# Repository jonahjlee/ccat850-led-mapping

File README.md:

# ccat850-led-mapping
CAD files for CCAT 850GHz LED mapping array PCB &amp; peripherals

This project contains various cad files relating to hardware required to perform LED mapping for CCAT's 850GHz module.
This project includes the following directories:
- ``led_mapper_850``
  - The defining the PCB for one rhombus of the LED mapper array. Contains the KiCAD project and some Python programs used to automate the LED/via/track layout.
- ``multiplexer`` - NO LONGER USED
  - The cable splitter used between the Arduino shield and the mapper array. Splits the inputs into 13 parallel 24-pin connectors. Since the PCB has been updated to use a single connector, this is no longer relevant to the project.
- ``collimator``
  - SOLIDWORKS CAD files for the collimator, which mounts to the array and nests each LED such that light is funneled one-to-one with the feedhorns. The old collimator CAD model can be found in [this onshape project](https://cad.onshape.com/documents/4a9874995d3b4039a34f4491/w/a61d1c1f9ee3ea8193c6d7eb/e/afbea4677e4648f6492246a2).

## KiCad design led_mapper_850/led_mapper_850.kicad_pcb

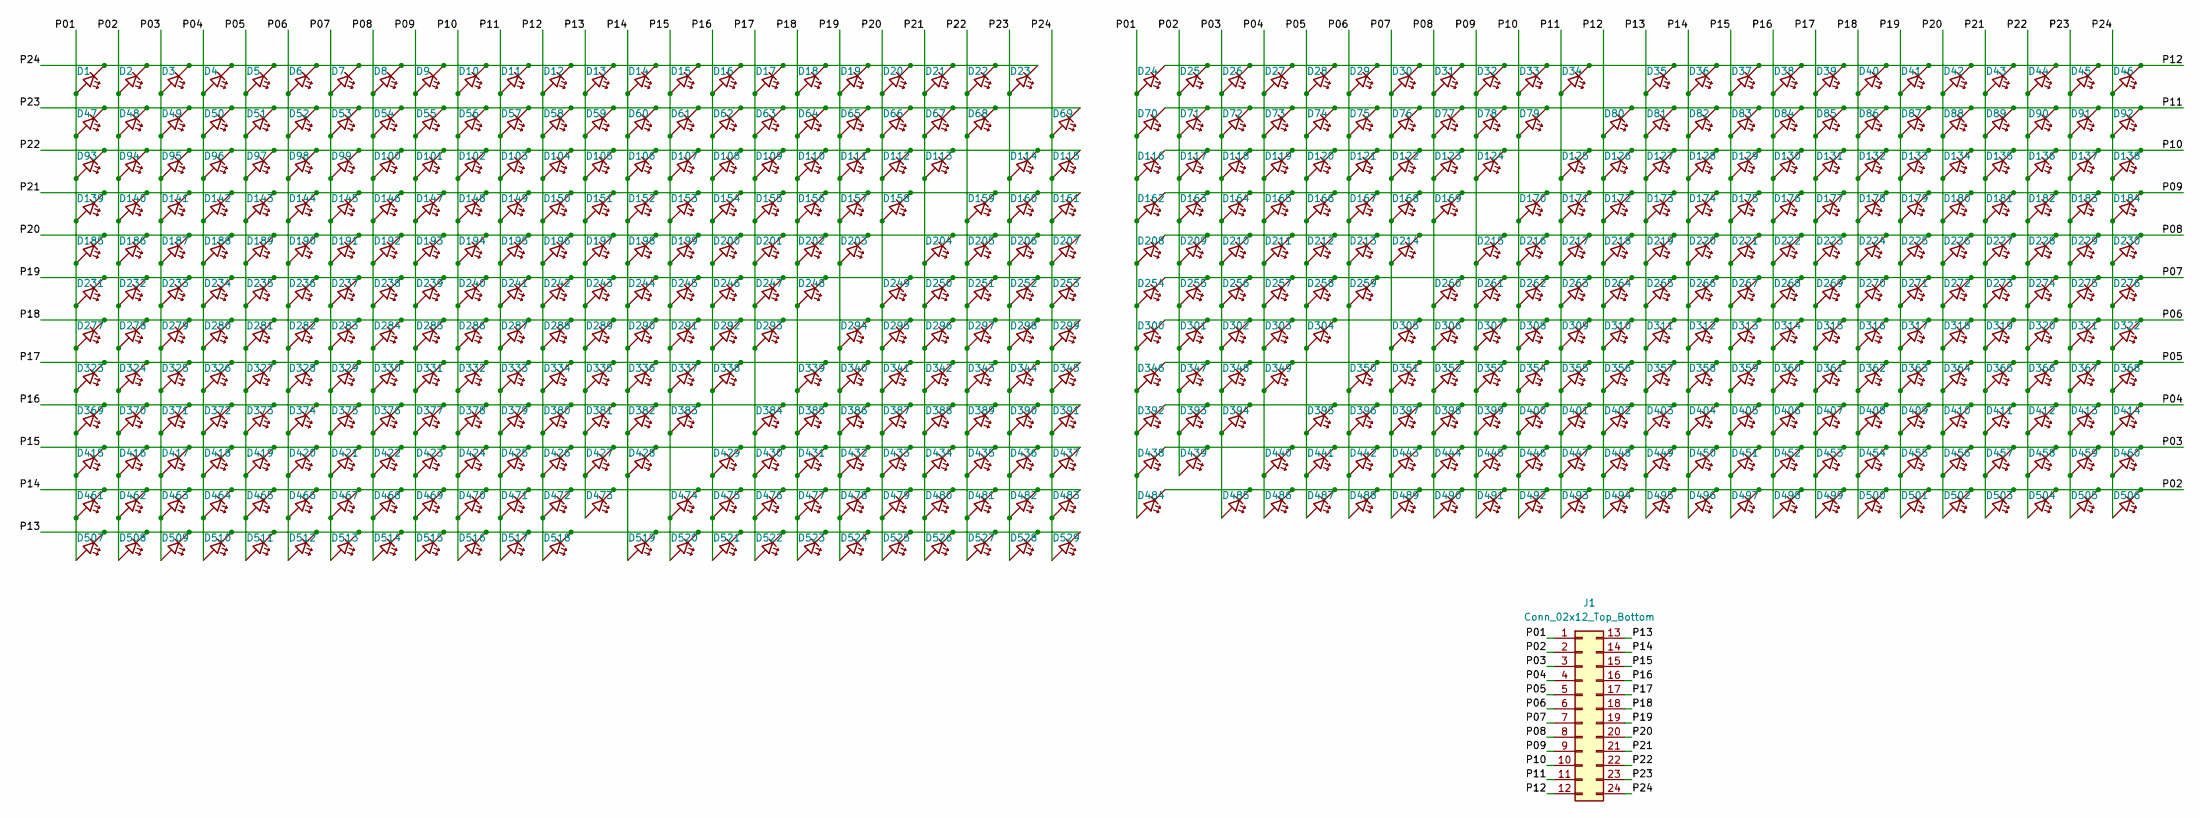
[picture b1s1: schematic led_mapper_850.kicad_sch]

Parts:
D1, D2, D3, D4, D5, D6, D7, D8, D9, D10, D11, D12, D13, D14, D15, D16, D17, D18, D19, D20, D21, D22, D23, D24, D25, D26, D27, D28, D29, D30, D31, D32, D33, D34, D35, D36, D37, D38, D39, D40, D41, D42, D43, D44, D45, D46, D47, D48, D49, D50, D51, D52, D53, D54, D55, D56, D57, D58, D59, D60, D61, D62, D63, D64, D65, D66, D67, D68, D69, D70, D71, D72, D73, D74, D75, D76, D77, D78, D79, D80, D81, D82, D83, D84, D85, D86, D87, D88, D89, D90, D91, D92, D93, D94, D95, D96, D97, D98, D99, D100, D101, D102, D103, D104, D105, D106, D107, D108, D109, D110, D111, D112, D113, D114, D115, D116, D117, D118, D119, D120, D121, D122, D123, D124, D125, D126, D127, D128, D129, D130, D131, D132, D133, D134, D135, D136, D137, D138, D139, D140, D141, D142, D143, D144, D145, D146, D147, D148, D149, D150, D151, D152, D153, D154, D155, D156, D157, D158, D159, D160, D161, D162, D163, D164, D165, D166, D167, D168, D169, D170, D171, D172, D173, D174, D175, D176, D177, D178, D179, D180, D181, D182, D183, D184, D185, D186, D187, D188, D189, D190, D191, D192, D193, D194, D195, D196, D197, D198, D199, D200, D201, D202, D203, D204, D205, D206, D207, D208, D209, D210, D211, D212, D213, D214, D215, D216, D217, D218, D219, D220, D221, D222, D223, D224, D225, D226, D227, D228, D229, D230, D231, D232, D233, D234, D235, D236, D237, D238, D239, D240, D241, D242, D243, D244, D245, D246, D247, D248, D249, D250, D251, D252, D253, D254, D255, D256, D257, D258, D259, D260, D261, D262, D263, D264, D265, D266, D267, D268, D269, D270, D271, D272, D273, D274, D275, D276, D277, D278, D279, D280, D281, D282, D283, D284, D285, D286, D287, D288, D289, D290, D291, D292, D293, D294, D295, D296, D297, D298, D299, D300, D301, D302, D303, D304, D305, D306, D307, D308, D309, D310, D311, D312, D313, D314, D315, D316, D317, D318, D319, D320, D321, D322, D323, D324, D325, D326, D327, D328, D329, D330, D331, D332, D333, D334, D335, D336, D337, D338, D339, D340, D341, D342, D343, D344, D345, D346, D347, D348, D349, D350, D351, D352, D353, D354, D355, D356, D357, D358, D359, D360, D361, D362, D363, D364, D365, D366, D367, D368, D369, D370, D371, D372, D373, D374, D375, D376, D377, D378, D379, D380, D381, D382, D383, D384, D385, D386, D387, D388, D389, D390, D391, D392, D393, D394, D395, D396, D397, D398, D399, D400, D401, D402, D403, D404, D405, D406, D407, D408, D409, D410, D411, D412, D413, D414, D415, D416, D417, D418, D419, D420, D421, D422, D423, D424, D425, D426, D427, D428, D429, D430, D431, D432, D433, D434, D435, D436, D437, D438, D439, D440, D441, D442, D443, D444, D445, D446, D447, D448, D449, D450, D451, D452, D453, D454, D455, D456, D457, D458, D459, D460, D461, D462, D463, D464, D465, D466, D467, D468, D469, D470, D471, D472, D473, D474, D475, D476, D477, D478, D479, D480, D481, D482, D483, D484, D485, D486, D487, D488, D489, D490, D491, D492, D493, D494, D495, D496, D497, D498, D499, D500, D501, D502, D503, D504, D505, D506, D507, D508, D509, D510, D511, D512, D513, D514, D515, D516, D517, D518, D519, D520, D521, D522, D523, D524, D525, D526, D527, D528, D529: LED; LED_0201_0603Metric
J1: Conn_02x12_Top_Bottom; PinSocket_2x12_P2.54mm_Vertical_SMD_custom

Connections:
/P01: D1.2 (A), D24.2 (A), D47.2 (A), D70.2 (A), D93.2 (A), D116.2 (A), D139.2 (A), D162.2 (A), D185.2 (A), D208.2 (A), D231.2 (A), D254.2 (A), D277.2 (A), D300.2 (A), D323.2 (A), D346.2 (A), D369.2 (A), D392.2 (A), D415.2 (A), D438.2 (A), D461.2 (A), D484.2 (A), D507.2 (A), J1.1
/P02: D2.2 (A), D25.2 (A), D48.2 (A), D71.2 (A), D94.2 (A), D117.2 (A), D140.2 (A), D163.2 (A), D186.2 (A), D209.2 (A), D232.2 (A), D255.2 (A), D278.2 (A), D301.2 (A), D324.2 (A), D347.2 (A), D370.2 (A), D393.2 (A), D416.2 (A), D439.2 (A), D462.2 (A), D484.1 (K), D485.1 (K), D486.1 (K), D487.1 (K), D488.1 (K), D489.1 (K), D490.1 (K), D491.1 (K), D492.1 (K), D493.1 (K), D494.1 (K), D495.1 (K), D496.1 (K), D497.1 (K), D498.1 (K), D499.1 (K), D500.1 (K), D501.1 (K), D502.1 (K), D503.1 (K), D504.1 (K), D505.1 (K), D506.1 (K), D508.2 (A), J1.2
/P03: D3.2 (A), D26.2 (A), D49.2 (A), D72.2 (A), D95.2 (A), D118.2 (A), D141.2 (A), D164.2 (A), D187.2 (A), D210.2 (A), D233.2 (A), D256.2 (A), D279.2 (A), D302.2 (A), D325.2 (A), D348.2 (A), D371.2 (A), D394.2 (A), D417.2 (A), D438.1 (K), D439.1 (K), D440.1 (K), D441.1 (K), D442.1 (K), D443.1 (K), D444.1 (K), D445.1 (K), D446.1 (K), D447.1 (K), D448.1 (K), D449.1 (K), D450.1 (K), D451.1 (K), D452.1 (K), D453.1 (K), D454.1 (K), D455.1 (K), D456.1 (K), D457.1 (K), D458.1 (K), D459.1 (K), D460.1 (K), D463.2 (A), D485.2 (A), D509.2 (A), J1.3
/P04: D4.2 (A), D27.2 (A), D50.2 (A), D73.2 (A), D96.2 (A), D119.2 (A), D142.2 (A), D165.2 (A), D188.2 (A), D211.2 (A), D234.2 (A), D257.2 (A), D280.2 (A), D303.2 (A), D326.2 (A), D349.2 (A), D372.2 (A), D392.1 (K), D393.1 (K), D394.1 (K), D395.1 (K), D396.1 (K), D397.1 (K), D398.1 (K), D399.1 (K), D400.1 (K), D401.1 (K), D402.1 (K), D403.1 (K), D404.1 (K), D405.1 (K), D406.1 (K), D407.1 (K), D408.1 (K), D409.1 (K), D410.1 (K), D411.1 (K), D412.1 (K), D413.1 (K), D414.1 (K), D418.2 (A), D440.2 (A), D464.2 (A), D486.2 (A), D510.2 (A), J1.4
/P05: D5.2 (A), D28.2 (A), D51.2 (A), D74.2 (A), D97.2 (A), D120.2 (A), D143.2 (A), D166.2 (A), D189.2 (A), D212.2 (A), D235.2 (A), D258.2 (A), D281.2 (A), D304.2 (A), D327.2 (A), D346.1 (K), D347.1 (K), D348.1 (K), D349.1 (K), D350.1 (K), D351.1 (K), D352.1 (K), D353.1 (K), D354.1 (K), D355.1 (K), D356.1 (K), D357.1 (K), D358.1 (K), D359.1 (K), D360.1 (K), D361.1 (K), D362.1 (K), D363.1 (K), D364.1 (K), D365.1 (K), D366.1 (K), D367.1 (K), D368.1 (K), D373.2 (A), D395.2 (A), D419.2 (A), D441.2 (A), D465.2 (A), D487.2 (A), D511.2 (A), J1.5
/P06: D6.2 (A), D29.2 (A), D52.2 (A), D75.2 (A), D98.2 (A), D121.2 (A), D144.2 (A), D167.2 (A), D190.2 (A), D213.2 (A), D236.2 (A), D259.2 (A), D282.2 (A), D300.1 (K), D301.1 (K), D302.1 (K), D303.1 (K), D304.1 (K), D305.1 (K), D306.1 (K), D307.1 (K), D308.1 (K), D309.1 (K), D310.1 (K), D311.1 (K), D312.1 (K), D313.1 (K), D314.1 (K), D315.1 (K), D316.1 (K), D317.1 (K), D318.1 (K), D319.1 (K), D320.1 (K), D321.1 (K), D322.1 (K), D328.2 (A), D350.2 (A), D374.2 (A), D396.2 (A), D420.2 (A), D442.2 (A), D466.2 (A), D488.2 (A), D512.2 (A), J1.6
/P07: D7.2 (A), D30.2 (A), D53.2 (A), D76.2 (A), D99.2 (A), D122.2 (A), D145.2 (A), D168.2 (A), D191.2 (A), D214.2 (A), D237.2 (A), D254.1 (K), D255.1 (K), D256.1 (K), D257.1 (K), D258.1 (K), D259.1 (K), D260.1 (K), D261.1 (K), D262.1 (K), D263.1 (K), D264.1 (K), D265.1 (K), D266.1 (K), D267.1 (K), D268.1 (K), D269.1 (K), D270.1 (K), D271.1 (K), D272.1 (K), D273.1 (K), D274.1 (K), D275.1 (K), D276.1 (K), D283.2 (A), D305.2 (A), D329.2 (A), D351.2 (A), D375.2 (A), D397.2 (A), D421.2 (A), D443.2 (A), D467.2 (A), D489.2 (A), D513.2 (A), J1.7
/P08: D8.2 (A), D31.2 (A), D54.2 (A), D77.2 (A), D100.2 (A), D123.2 (A), D146.2 (A), D169.2 (A), D192.2 (A), D208.1 (K), D209.1 (K), D210.1 (K), D211.1 (K), D212.1 (K), D213.1 (K), D214.1 (K), D215.1 (K), D216.1 (K), D217.1 (K), D218.1 (K), D219.1 (K), D220.1 (K), D221.1 (K), D222.1 (K), D223.1 (K), D224.1 (K), D225.1 (K), D226.1 (K), D227.1 (K), D228.1 (K), D229.1 (K), D230.1 (K), D238.2 (A), D260.2 (A), D284.2 (A), D306.2 (A), D330.2 (A), D352.2 (A), D376.2 (A), D398.2 (A), D422.2 (A), D444.2 (A), D468.2 (A), D490.2 (A), D514.2 (A), J1.8
/P09: D9.2 (A), D32.2 (A), D55.2 (A), D78.2 (A), D101.2 (A), D124.2 (A), D147.2 (A), D162.1 (K), D163.1 (K), D164.1 (K), D165.1 (K), D166.1 (K), D167.1 (K), D168.1 (K), D169.1 (K), D170.1 (K), D171.1 (K), D172.1 (K), D173.1 (K), D174.1 (K), D175.1 (K), D176.1 (K), D177.1 (K), D178.1 (K), D179.1 (K), D180.1 (K), D181.1 (K), D182.1 (K), D183.1 (K), D184.1 (K), D193.2 (A), D215.2 (A), D239.2 (A), D261.2 (A), D285.2 (A), D307.2 (A), D331.2 (A), D353.2 (A), D377.2 (A), D399.2 (A), D423.2 (A), D445.2 (A), D469.2 (A), D491.2 (A), D515.2 (A), J1.9
/P10: D10.2 (A), D33.2 (A), D56.2 (A), D79.2 (A), D102.2 (A), D116.1 (K), D117.1 (K), D118.1 (K), D119.1 (K), D120.1 (K), D121.1 (K), D122.1 (K), D123.1 (K), D124.1 (K), D125.1 (K), D126.1 (K), D127.1 (K), D128.1 (K), D129.1 (K), D130.1 (K), D131.1 (K), D132.1 (K), D133.1 (K), D134.1 (K), D135.1 (K), D136.1 (K), D137.1 (K), D138.1 (K), D148.2 (A), D170.2 (A), D194.2 (A), D216.2 (A), D240.2 (A), D262.2 (A), D286.2 (A), D308.2 (A), D332.2 (A), D354.2 (A), D378.2 (A), D400.2 (A), D424.2 (A), D446.2 (A), D470.2 (A), D492.2 (A), D516.2 (A), J1.10
/P11: D11.2 (A), D34.2 (A), D57.2 (A), D70.1 (K), D71.1 (K), D72.1 (K), D73.1 (K), D74.1 (K), D75.1 (K), D76.1 (K), D77.1 (K), D78.1 (K), D79.1 (K), D80.1 (K), D81.1 (K), D82.1 (K), D83.1 (K), D84.1 (K), D85.1 (K), D86.1 (K), D87.1 (K), D88.1 (K), D89.1 (K), D90.1 (K), D91.1 (K), D92.1 (K), D103.2 (A), D125.2 (A), D149.2 (A), D171.2 (A), D195.2 (A), D217.2 (A), D241.2 (A), D263.2 (A), D287.2 (A), D309.2 (A), D333.2 (A), D355.2 (A), D379.2 (A), D401.2 (A), D425.2 (A), D447.2 (A), D471.2 (A), D493.2 (A), D517.2 (A), J1.11
/P12: D12.2 (A), D24.1 (K), D25.1 (K), D26.1 (K), D27.1 (K), D28.1 (K), D29.1 (K), D30.1 (K), D31.1 (K), D32.1 (K), D33.1 (K), D34.1 (K), D35.1 (K), D36.1 (K), D37.1 (K), D38.1 (K), D39.1 (K), D40.1 (K), D41.1 (K), D42.1 (K), D43.1 (K), D44.1 (K), D45.1 (K), D46.1 (K), D58.2 (A), D80.2 (A), D104.2 (A), D126.2 (A), D150.2 (A), D172.2 (A), D196.2 (A), D218.2 (A), D242.2 (A), D264.2 (A), D288.2 (A), D310.2 (A), D334.2 (A), D356.2 (A), D380.2 (A), D402.2 (A), D426.2 (A), D448.2 (A), D472.2 (A), D494.2 (A), D518.2 (A), J1.12
/P13: D13.2 (A), D35.2 (A), D59.2 (A), D81.2 (A), D105.2 (A), D127.2 (A), D151.2 (A), D173.2 (A), D197.2 (A), D219.2 (A), D243.2 (A), D265.2 (A), D289.2 (A), D311.2 (A), D335.2 (A), D357.2 (A), D381.2 (A), D403.2 (A), D427.2 (A), D449.2 (A), D473.2 (A), D495.2 (A), D507.1 (K), D508.1 (K), D509.1 (K), D510.1 (K), D511.1 (K), D512.1 (K), D513.1 (K), D514.1 (K), D515.1 (K), D516.1 (K), D517.1 (K), D518.1 (K), D519.1 (K), D520.1 (K), D521.1 (K), D522.1 (K), D523.1 (K), D524.1 (K), D525.1 (K), D526.1 (K), D527.1 (K), D528.1 (K), D529.1 (K), J1.13
/P14: D14.2 (A), D36.2 (A), D60.2 (A), D82.2 (A), D106.2 (A), D128.2 (A), D152.2 (A), D174.2 (A), D198.2 (A), D220.2 (A), D244.2 (A), D266.2 (A), D290.2 (A), D312.2 (A), D336.2 (A), D358.2 (A), D382.2 (A), D404.2 (A), D428.2 (A), D450.2 (A), D461.1 (K), D462.1 (K), D463.1 (K), D464.1 (K), D465.1 (K), D466.1 (K), D467.1 (K), D468.1 (K), D469.1 (K), D470.1 (K), D471.1 (K), D472.1 (K), D473.1 (K), D474.1 (K), D475.1 (K), D476.1 (K), D477.1 (K), D478.1 (K), D479.1 (K), D480.1 (K), D481.1 (K), D482.1 (K), D483.1 (K), D496.2 (A), D519.2 (A), J1.14
/P15: D15.2 (A), D37.2 (A), D61.2 (A), D83.2 (A), D107.2 (A), D129.2 (A), D153.2 (A), D175.2 (A), D199.2 (A), D221.2 (A), D245.2 (A), D267.2 (A), D291.2 (A), D313.2 (A), D337.2 (A), D359.2 (A), D383.2 (A), D405.2 (A), D415.1 (K), D416.1 (K), D417.1 (K), D418.1 (K), D419.1 (K), D420.1 (K), D421.1 (K), D422.1 (K), D423.1 (K), D424.1 (K), D425.1 (K), D426.1 (K), D427.1 (K), D428.1 (K), D429.1 (K), D430.1 (K), D431.1 (K), D432.1 (K), D433.1 (K), D434.1 (K), D435.1 (K), D436.1 (K), D437.1 (K), D451.2 (A), D474.2 (A), D497.2 (A), D520.2 (A), J1.15
/P16: D16.2 (A), D38.2 (A), D62.2 (A), D84.2 (A), D108.2 (A), D130.2 (A), D154.2 (A), D176.2 (A), D200.2 (A), D222.2 (A), D246.2 (A), D268.2 (A), D292.2 (A), D314.2 (A), D338.2 (A), D360.2 (A), D369.1 (K), D370.1 (K), D371.1 (K), D372.1 (K), D373.1 (K), D374.1 (K), D375.1 (K), D376.1 (K), D377.1 (K), D378.1 (K), D379.1 (K), D380.1 (K), D381.1 (K), D382.1 (K), D383.1 (K), D384.1 (K), D385.1 (K), D386.1 (K), D387.1 (K), D388.1 (K), D389.1 (K), D390.1 (K), D391.1 (K), D406.2 (A), D429.2 (A), D452.2 (A), D475.2 (A), D498.2 (A), D521.2 (A), J1.16
/P17: D17.2 (A), D39.2 (A), D63.2 (A), D85.2 (A), D109.2 (A), D131.2 (A), D155.2 (A), D177.2 (A), D201.2 (A), D223.2 (A), D247.2 (A), D269.2 (A), D293.2 (A), D315.2 (A), D323.1 (K), D324.1 (K), D325.1 (K), D326.1 (K), D327.1 (K), D328.1 (K), D329.1 (K), D330.1 (K), D331.1 (K), D332.1 (K), D333.1 (K), D334.1 (K), D335.1 (K), D336.1 (K), D337.1 (K), D338.1 (K), D339.1 (K), D340.1 (K), D341.1 (K), D342.1 (K), D343.1 (K), D344.1 (K), D345.1 (K), D361.2 (A), D384.2 (A), D407.2 (A), D430.2 (A), D453.2 (A), D476.2 (A), D499.2 (A), D522.2 (A), J1.17
/P18: D18.2 (A), D40.2 (A), D64.2 (A), D86.2 (A), D110.2 (A), D132.2 (A), D156.2 (A), D178.2 (A), D202.2 (A), D224.2 (A), D248.2 (A), D270.2 (A), D277.1 (K), D278.1 (K), D279.1 (K), D280.1 (K), D281.1 (K), D282.1 (K), D283.1 (K), D284.1 (K), D285.1 (K), D286.1 (K), D287.1 (K), D288.1 (K), D289.1 (K), D290.1 (K), D291.1 (K), D292.1 (K), D293.1 (K), D294.1 (K), D295.1 (K), D296.1 (K), D297.1 (K), D298.1 (K), D299.1 (K), D316.2 (A), D339.2 (A), D362.2 (A), D385.2 (A), D408.2 (A), D431.2 (A), D454.2 (A), D477.2 (A), D500.2 (A), D523.2 (A), J1.18
/P19: D19.2 (A), D41.2 (A), D65.2 (A), D87.2 (A), D111.2 (A), D133.2 (A), D157.2 (A), D179.2 (A), D203.2 (A), D225.2 (A), D231.1 (K), D232.1 (K), D233.1 (K), D234.1 (K), D235.1 (K), D236.1 (K), D237.1 (K), D238.1 (K), D239.1 (K), D240.1 (K), D241.1 (K), D242.1 (K), D243.1 (K), D244.1 (K), D245.1 (K), D246.1 (K), D247.1 (K), D248.1 (K), D249.1 (K), D250.1 (K), D251.1 (K), D252.1 (K), D253.1 (K), D271.2 (A), D294.2 (A), D317.2 (A), D340.2 (A), D363.2 (A), D386.2 (A), D409.2 (A), D432.2 (A), D455.2 (A), D478.2 (A), D501.2 (A), D524.2 (A), J1.19
/P20: D20.2 (A), D42.2 (A), D66.2 (A), D88.2 (A), D112.2 (A), D134.2 (A), D158.2 (A), D180.2 (A), D185.1 (K), D186.1 (K), D187.1 (K), D188.1 (K), D189.1 (K), D190.1 (K), D191.1 (K), D192.1 (K), D193.1 (K), D194.1 (K), D195.1 (K), D196.1 (K), D197.1 (K), D198.1 (K), D199.1 (K), D200.1 (K), D201.1 (K), D202.1 (K), D203.1 (K), D204.1 (K), D205.1 (K), D206.1 (K), D207.1 (K), D226.2 (A), D249.2 (A), D272.2 (A), D295.2 (A), D318.2 (A), D341.2 (A), D364.2 (A), D387.2 (A), D410.2 (A), D433.2 (A), D456.2 (A), D479.2 (A), D502.2 (A), D525.2 (A), J1.20
/P21: D21.2 (A), D43.2 (A), D67.2 (A), D89.2 (A), D113.2 (A), D135.2 (A), D139.1 (K), D140.1 (K), D141.1 (K), D142.1 (K), D143.1 (K), D144.1 (K), D145.1 (K), D146.1 (K), D147.1 (K), D148.1 (K), D149.1 (K), D150.1 (K), D151.1 (K), D152.1 (K), D153.1 (K), D154.1 (K), D155.1 (K), D156.1 (K), D157.1 (K), D158.1 (K), D159.1 (K), D160.1 (K), D161.1 (K), D181.2 (A), D204.2 (A), D227.2 (A), D250.2 (A), D273.2 (A), D296.2 (A), D319.2 (A), D342.2 (A), D365.2 (A), D388.2 (A), D411.2 (A), D434.2 (A), D457.2 (A), D480.2 (A), D503.2 (A), D526.2 (A), J1.21
/P22: D22.2 (A), D44.2 (A), D68.2 (A), D90.2 (A), D93.1 (K), D94.1 (K), D95.1 (K), D96.1 (K), D97.1 (K), D98.1 (K), D99.1 (K), D100.1 (K), D101.1 (K), D102.1 (K), D103.1 (K), D104.1 (K), D105.1 (K), D106.1 (K), D107.1 (K), D108.1 (K), D109.1 (K), D110.1 (K), D111.1 (K), D112.1 (K), D113.1 (K), D114.1 (K), D115.1 (K), D136.2 (A), D159.2 (A), D182.2 (A), D205.2 (A), D228.2 (A), D251.2 (A), D274.2 (A), D297.2 (A), D320.2 (A), D343.2 (A), D366.2 (A), D389.2 (A), D412.2 (A), D435.2 (A), D458.2 (A), D481.2 (A), D504.2 (A), D527.2 (A), J1.22
/P23: D23.2 (A), D45.2 (A), D47.1 (K), D48.1 (K), D49.1 (K), D50.1 (K), D51.1 (K), D52.1 (K), D53.1 (K), D54.1 (K), D55.1 (K), D56.1 (K), D57.1 (K), D58.1 (K), D59.1 (K), D60.1 (K), D61.1 (K), D62.1 (K), D63.1 (K), D64.1 (K), D65.1 (K), D66.1 (K), D67.1 (K), D68.1 (K), D69.1 (K), D91.2 (A), D114.2 (A), D137.2 (A), D160.2 (A), D183.2 (A), D206.2 (A), D229.2 (A), D252.2 (A), D275.2 (A), D298.2 (A), D321.2 (A), D344.2 (A), D367.2 (A), D390.2 (A), D413.2 (A), D436.2 (A), D459.2 (A), D482.2 (A), D505.2 (A), D528.2 (A), J1.23
/P24: D1.1 (K), D2.1 (K), D3.1 (K), D4.1 (K), D5.1 (K), D6.1 (K), D7.1 (K), D8.1 (K), D9.1 (K), D10.1 (K), D11.1 (K), D12.1 (K), D13.1 (K), D14.1 (K), D15.1 (K), D16.1 (K), D17.1 (K), D18.1 (K), D19.1 (K), D20.1 (K), D21.1 (K), D22.1 (K), D23.1 (K), D46.2 (A), D69.2 (A), D92.2 (A), D115.2 (A), D138.2 (A), D161.2 (A), D184.2 (A), D207.2 (A), D230.2 (A), D253.2 (A), D276.2 (A), D299.2 (A), D322.2 (A), D345.2 (A), D368.2 (A), D391.2 (A), D414.2 (A), D437.2 (A), D460.2 (A), D483.2 (A), D506.2 (A), D529.2 (A), J1.24

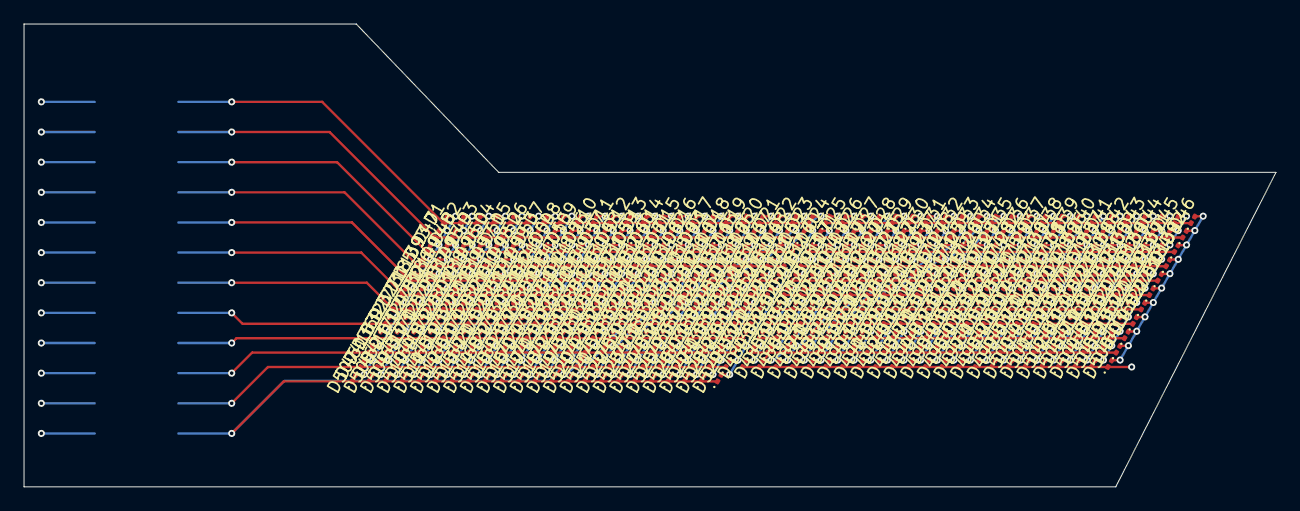
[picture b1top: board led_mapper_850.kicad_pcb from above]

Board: 4 copper layers, 105.5 x 39.0 mm, 530 parts (1 on the bottom side), 24 nets.

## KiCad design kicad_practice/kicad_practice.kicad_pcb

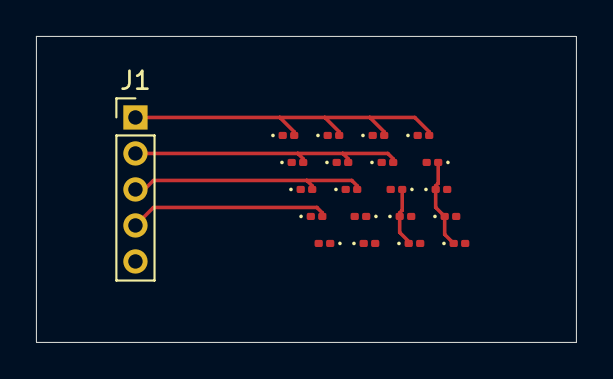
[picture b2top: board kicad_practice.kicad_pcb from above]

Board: 2 copper layers, 30.0 x 17.0 mm, 21 parts (0 on the bottom side), 5 nets.

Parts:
D1, D2, D3, D4, D5, D6, D7, D8, D9, D10, D11, D12, D13, D14, D15, D16, D17, D18, D19, D20: LED_45deg; LED_0201_0603Metric
J1: Conn_01x05; PinHeader_1x05_P2.00mm_Vertical

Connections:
unnamed: D1.2 (A), D2.2 (A), D4.2 (A), D5.1 (K), D7.1 (K), D10.2 (A), D15.1 (K), D19.1 (K), J1.4
unnamed: D1.1 (K), D8.2 (A), D12.1 (K), D13.1 (K), D14.2 (A), D15.2 (A), D16.1 (K), D17.2 (A), J1.2
unnamed: D3.2 (A), D6.2 (A), D7.2 (A), D8.1 (K), D9.1 (K), D10.1 (K), D11.1 (K), D13.2 (A), J1.3
unnamed: D4.1 (K), D6.1 (K), D11.2 (A), D12.2 (A), D14.1 (K), D18.2 (A), D19.2 (A), D20.1 (K), J1.1
unnamed: D2.1 (K), D3.1 (K), D5.2 (A), D9.2 (A), D16.2 (A), D17.1 (K), D18.1 (K), D20.2 (A), J1.5

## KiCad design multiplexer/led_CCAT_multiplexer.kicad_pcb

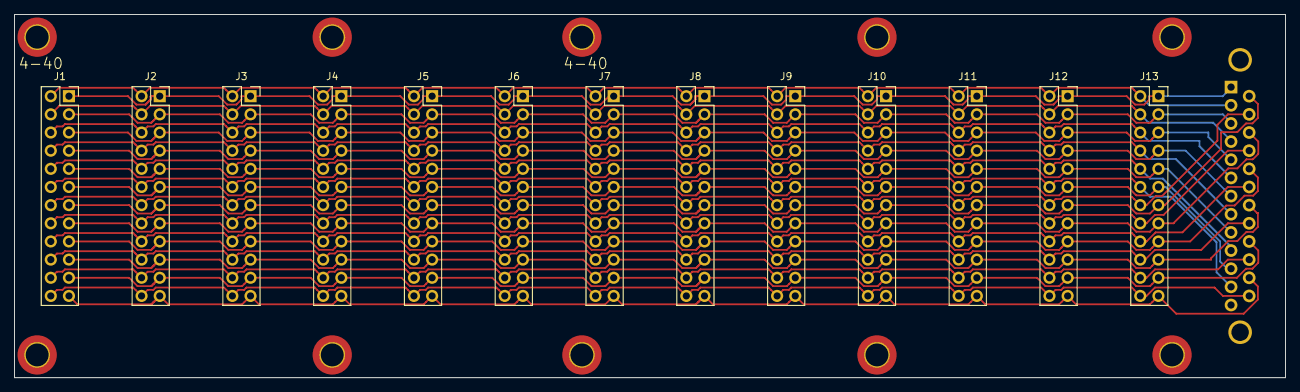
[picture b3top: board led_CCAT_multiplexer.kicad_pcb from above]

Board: 2 copper layers, 177.8 x 50.8 mm, 14 parts (1 on the bottom side), 25 nets.

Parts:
J1, J2, J3, J4, J5, J6, J7, J8, J9, J10, J11, J12, J13: Conn_02x12_Top_Bottom; PinSocket_2x12_P2.54mm_Vertical
J14: DB25_Female_MountingHoles; 25_pin_micro_D_male_straight_mount_pdb_wide_spacing

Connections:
/pin1: J1.1, J2.1, J3.1, J4.1, J5.1, J6.1, J7.1, J8.1, J9.1, J10.1, J11.1, J12.1, J13.1, J14.1
/pin2: J1.2, J2.2, J3.2, J4.2, J5.2, J6.2, J7.2, J8.2, J9.2, J10.2, J11.2, J12.2, J13.2, J14.2
/pin3: J1.3, J2.3, J3.3, J4.3, J5.3, J6.3, J7.3, J8.3, J9.3, J10.3, J11.3, J12.3, J13.3, J14.3
/pin4: J1.4, J2.4, J3.4, J4.4, J5.4, J6.4, J7.4, J8.4, J9.4, J10.4, J11.4, J12.4, J13.4, J14.4
/pin5: J1.5, J2.5, J3.5, J4.5, J5.5, J6.5, J7.5, J8.5, J9.5, J10.5, J11.5, J12.5, J13.5, J14.5
/pin6: J1.6, J2.6, J3.6, J4.6, J5.6, J6.6, J7.6, J8.6, J9.6, J10.6, J11.6, J12.6, J13.6, J14.6
/pin7: J1.7, J2.7, J3.7, J4.7, J5.7, J6.7, J7.7, J8.7, J9.7, J10.7, J11.7, J12.7, J13.7, J14.7
/pin8: J1.8, J2.8, J3.8, J4.8, J5.8, J6.8, J7.8, J8.8, J9.8, J10.8, J11.8, J12.8, J13.8, J14.8
/pin9: J1.9, J2.9, J3.9, J4.9, J5.9, J6.9, J7.9, J8.9, J9.9, J10.9, J11.9, J12.9, J13.9, J14.9
/pin10: J1.10, J2.10, J3.10, J4.10, J5.10, J6.10, J7.10, J8.10, J9.10, J10.10, J11.10, J12.10, J13.10, J14.10
/pin11: J1.11, J2.11, J3.11, J4.11, J5.11, J6.11, J7.11, J8.11, J9.11, J10.11, J11.11, J12.11, J13.11, J14.11
/pin12: J1.12, J2.12, J3.12, J4.12, J5.12, J6.12, J7.12, J8.12, J9.12, J10.12, J11.12, J12.12, J13.12, J14.12
/pin13: J1.13, J2.13, J3.13, J4.13, J5.13, J6.13, J7.13, J8.13, J9.13, J10.13, J11.13, J12.13, J13.13, J14.14
/pin14: J1.14, J2.14, J3.14, J4.14, J5.14, J6.14, J7.14, J8.14, J9.14, J10.14, J11.14, J12.14, J13.14, J14.15
/pin15: J1.15, J2.15, J3.15, J4.15, J5.15, J6.15, J7.15, J8.15, J9.15, J10.15, J11.15, J12.15, J13.15, J14.16
/pin16: J1.16, J2.16, J3.16, J4.16, J5.16, J6.16, J7.16, J8.16, J9.16, J10.16, J11.16, J12.16, J13.16, J14.17
/pin17: J1.17, J2.17, J3.17, J4.17, J5.17, J6.17, J7.17, J8.17, J9.17, J10.17, J11.17, J12.17, J13.17, J14.18
/pin18: J1.18, J2.18, J3.18, J4.18, J5.18, J6.18, J7.18, J8.18, J9.18, J10.18, J11.18, J12.18, J13.18, J14.19
/pin19: J1.19, J2.19, J3.19, J4.19, J5.19, J6.19, J7.19, J8.19, J9.19, J10.19, J11.19, J12.19, J13.19, J14.20
/pin20: J1.20, J2.20, J3.20, J4.20, J5.20, J6.20, J7.20, J8.20, J9.20, J10.20, J11.20, J12.20, J13.20, J14.21
/pin21: J1.21, J2.21, J3.21, J4.21, J5.21, J6.21, J7.21, J8.21, J9.21, J10.21, J11.21, J12.21, J13.21, J14.22
/pin22: J1.22, J2.22, J3.22, J4.22, J5.22, J6.22, J7.22, J8.22, J9.22, J10.22, J11.22, J12.22, J13.22, J14.23
/pin23: J1.23, J2.23, J3.23, J4.23, J5.23, J6.23, J7.23, J8.23, J9.23, J10.23, J11.23, J12.23, J13.23, J14.24
/pin24: J1.24, J2.24, J3.24, J4.24, J5.24, J6.24, J7.24, J8.24, J9.24, J10.24, J11.24, J12.24, J13.24, J14.25
GND: J14.0 (PAD), J14.13

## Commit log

2025-02-21 add kicad project
2025-02-21 add kicad practice project
2025-02-21 run ERC & fix connections
2025-02-21 associate footprints
2025-02-21 fix mistakes on diagonal
2025-02-21 load schematic into pcb
2025-02-21 arrange schematic to match array geometry
2025-02-21 fix horizontal connections
2025-02-21 remove old file
2025-02-21 copy/flip/rotate shenanigans to organise refdes into rows
    after diagonals are collapsed left-right (such that there are 12 rows), references are simply listed left to right then top to bottom
2025-02-21 fix missing wire & references
2025-02-21 start making python layout script
2025-02-21 add spacing constants
2025-02-21 gitignore - ignore *.pyc
2025-02-21 add reference file
2025-02-22 lay out network from pcb positions
2025-02-22 add file doc
2025-02-25 fix wire disconnect
2025-02-25 update pcb from schematic
2025-02-25 code to place vias & functional interface for placements
2025-02-25 place vias
2025-02-26 wire most traces
2025-02-26 update remote
2025-02-26 complete wiring after rotating leds
2025-02-26 split into four networks
2025-02-27 add docstrings
2025-02-27 refactor: create main placing script
2025-02-27 draft outline
2025-02-27 begin automating whole array
2025-02-27 sync pcb
2025-02-27 short front rows
2025-02-28 remove unused file
2025-02-28 more code & manual edits
2025-02-28 automate inner layer generation
2025-03-01 first complete wiring - some DRC errors
2025-03-03 update gitignore
2025-03-03 v0 compete - all DRC passing (except silkscreen)
2025-03-03 rename single net schematic
2025-03-03 sync - misc experimentation
2025-03-03 add multiplexer
2025-03-03 add 6 connectors to multiplexer
2025-03-03 clean up front connector wires
2025-03-03 more wire cleanup
2025-03-04 add collimator dxf for comparison
2025-03-04 remove practice project
2025-03-04 restore copper zones
2025-03-04 use double quotes
2025-03-04 begin position_mapping code
2025-03-05 add position mapping code
2025-03-05 refactor directories
2025-03-05 remove sch
2025-03-05 remove auto generated import
2025-03-05 continue position mapper
2025-03-06 update nb
2025-03-06 add some parameters
2025-03-06 use single connector
2025-03-06 start placing & routing
2025-03-06 stitch columns automatically
2025-03-06 rework row vias & front row shorts
2025-03-07 refactor - no state necessary for method calls
2025-03-07 automate in2 connector cables
2025-03-07 remove unneccesary vias by shorting more front pins for net 1/3
2025-03-07 improve mapping tool
2025-03-07 automate inner layer gen
2025-03-07 fix extra track
2025-03-07 complete single_connector model!
2025-03-08 rename v0->v1
2025-03-08 add v2 gerber
2025-03-08 add led part number - XINGLIGHT Red 0201
2025-03-08 add fabrication outputs for previewing PCBA quote
2025-03-10 add collimator CAD files
2025-03-10 update pcb edge cuts to be 3mm on top & left
2025-03-11 align collimator & pcb model in CAD
2025-03-11 tighten connector position
2025-03-12 fix critical schematic error - wrong pins
2025-03-12 continue position mapping code
2025-03-12 sync cad file
2025-03-12 rebuild board layout to fix net errors
2025-03-12 fix network issues (pin name mismatch)
2025-03-12 set hole diameter to 0.9mm
2025-03-13 build exact board outline
2025-03-14 sync project
2025-03-14 add mirrored rhombus
2025-03-14 mirror rhombus
2025-03-14 update board outline
2025-03-14 complete assembly
2025-03-17 clean up assembly
2025-03-19 sync local work
2025-03-21 fix anode cathode mixup and get pin arrays for all networks
2025-03-21 add clarifying comment
2025-03-21 rename folder to "rhombus"
2025-03-26 Sync changes: update holes to 2.2mm, change footprint to match datasheet
2025-03-26 missed file - schematic
2025-03-26 add production outputs
2025-03-26 add csv files
2025-04-11 add step file
2025-04-15 add collimator dxf
2025-04-15 fix dxf for prod
2025-04-15 add 1/4in step file
